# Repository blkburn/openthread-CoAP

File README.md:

# openthread-CoAP

This repository contains multiple projects relating to the OpenThread wireless protocol.

- thread_sensor_cc2652
- hardware

---

## thread_sensor_cc2652

The sensor design is based on the Texas Instruments cc2652, with the hardware is identical to the Zigbee sensor design in: https://github.com/blkburn/zigbee/tree/main/hardware/zed_v1  
With the sensor controller code in:
https://github.com/blkburn/zigbee/tree/main/sensor_controller

This is a Thread Sleepy End Device based on the Texas Instruments CC2652R1. It supports the following sensors (with build switches):

- AHT10 Temperature and Humidity Sensor
- PIR Movement Sensor
- Reed Switch (Door opening sensor)
- Mains Energy Monitor (split coil current transformer)

The Sensor Controller handles all the sensor communications, while the main process handles the Thread/CoAP stack and a custom task is used to process sensor reading and construct CoAP messages.

Master branch is currently built with:

- CCStudio version: 11.1.0.00011
- SDK: simplelink_cc13x2_26x2_sdk_5_20_00_52

---

## Hardware

KiCad schematic and PCB designs. Both boards have be manufactured, tested, and working.

### Thread Border Router

Based on the nrf52840 module from Minew (MS88SF23). It is a daughter board for the Orange Pi Zero 2 (http://www.orangepi.org/Orange%20Pi%20Zero2/). The Orange Pi uses an Allwinner H616 processor and comfortably runs Ubuntu or Debian Linux (plus much cheaper than a Raspberry Pi 4).

## todo: description of compiling the border router software. Requires Ubuntu.

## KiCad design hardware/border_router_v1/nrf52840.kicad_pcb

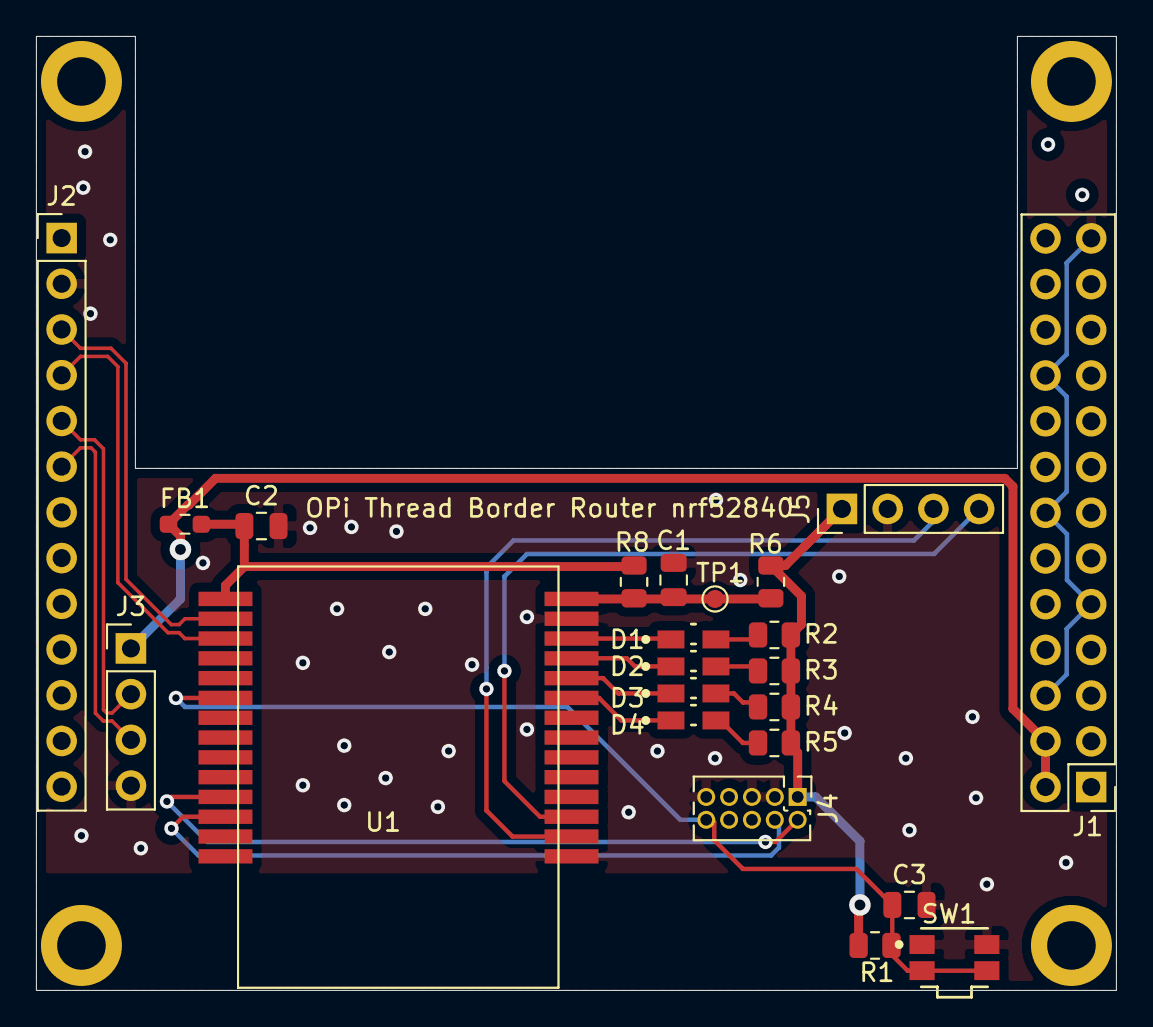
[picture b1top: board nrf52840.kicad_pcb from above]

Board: 2 copper layers, 60.0 x 53.0 mm, 27 parts (0 on the bottom side), 23 nets.

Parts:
C1, C2, C3: 100n; C_0805_2012Metric
D1, D2, D3, D4: LED; Lite-On-LTST-S220KRKT-0-0-0
FB1: BLM18HE152SN1D; R_0603_1608Metric_Pad0.98x0.95mm_HandSolder
H1, H2, H3, H4: MountingHole; MountingHole_2.7mm_M2.5_ISO14580_Pad
J1: Conn_02x13_Odd_Even; PinHeader_2x13_P2.54mm_Vertical
J2: Conn_01x13_Female; PinHeader_1x13_P2.54mm_Vertical
J3: Conn_01x04_Male; PinHeader_1x04_P2.54mm_Vertical
J4: Conn_02x05_Odd_Even; PinHeader_2x05_P1.27mm_Vertical
J5: Conn_01x04; PinHeader_1x04_P2.54mm_Vertical
R1: 10k; R_0805_2012Metric
R2, R3, R4, R5: 220; R_0805_2012Metric
R6: 0; R_0805_2012Metric
R8: 4R7; R_0805_2012Metric
SW1: EVQ-P7A01P-switch2; Panasonic-EVQ-P7A01P-0-0-MFG
TP1: TP; TestPoint_Pad_D1.0mm
U1: MS88SF2_nRF52840; MS88SF2

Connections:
+3V3: J1.1, J1.17
+5V: FB1.1, J1.2, J1.4, J2.1, J3.1
/SWDCLK: J4.4, U1.26
/SWDIO: J4.2, U1.25
/USB2_D+: J2.4, U1.17
/USB2_D-: J2.3, U1.16
/USB3_D+: J2.6, J3.3
/USB3_D-: J2.5, J3.2
/nrf_SCL: J5.3, U1.2
/nrf_SDA: J5.4, U1.3
GND: C1.2, C2.2, C3.2, J1.6, J1.9, J1.14, J1.20, J1.25, J2.2, J3.4, J4.3, J4.5, J4.9, J5.2, SW1.1, SW1.1', U1.1, U1.13
unnamed: C2.1, FB1.2, R8.2, U1.15
unnamed: C3.1, J4.10, R1.2, SW1.2, SW1.2', U1.20
unnamed: D1.1, U1.12
unnamed: D1.2, R2.2
unnamed: D2.1, U1.11
unnamed: D2.2, R3.2
unnamed: D3.1, U1.10
unnamed: D3.2, R4.2
unnamed: D4.1, U1.9
unnamed: D4.2, R5.2
VDD: J4.1, J5.1, R1.1, R2.1, R3.1, R4.1, R5.1, R6.1
VDDF: C1.1, R6.2, R8.1, TP1.1, U1.14

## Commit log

2022-02-10 readme fix
